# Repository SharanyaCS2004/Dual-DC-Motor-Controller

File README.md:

# 🚗 Dual DC Motor Controller (L298N-based)

This project is a simple and efficient **dual DC motor driver module** based on the **L298N** IC. It's designed to drive two DC motors with full H-bridge control and includes protection diodes and input/output connectors. Ideal for robotics kits, embedded systems, and motor control learners.

---

## 📦 Features

- ✅ Based on L298N dual H-bridge motor driver IC  
- ✅ Supports 2 DC motors with direction control  
- ✅ Optional PWM speed control via ENA/ENB  
- ✅ Flyback diodes (1N4007) for protection  
- ✅ Terminal blocks for motors and power  
- ✅ Logic level input via header pins  
- ✅ 2-layer compact PCB layout

---

## 🧠 Skills Demonstrated

- High-current trace routing  
- Silkscreen clarity for connectors  
- Power and thermal management  
- Modular and testable design

---

## ⚙️ Schematic Overview

- Motor driver: **L298N**
- Input voltage: **12V** regulated to **5V** using **7805**
- Control pins: **IN1–IN4**, **ENA**, **ENB**
- Output pins: **OUT1–OUT4** to motors
- Protection: **1N4007 diodes** for back-EMF across motor terminals

---

## 🔌 Pin Configuration

| Pin        | Function         |
|------------|------------------|
| IN1–IN4    | Direction control|
| ENA / ENB  | Enable/PWM input |
| OUT1–OUT4  | Motor outputs    |
| VS         | Motor power (12V)|
| VSS        | Logic power (5V) |
| GND        | Ground           |

---

## 📁 File Structure
``` Dual DC Motor Controller/
├── Dual DC Motor Controller.kicad_sch # Schematic file
├── Dual DC Motor Controller.kicad_pcb # PCB layout file
├── Dual DC Motor Controller.kicad_pro # KiCad project file
├── Dual DC Motor Controller.kicad_prl # KiCad netlist-related
├── Dual DC Motor Controller.kicad_sch-bak # Schematic backup
├── fp-info-cache # KiCad footprint cache
├── gerber/ # Gerber manufacturing files
├── Images/
│ ├── DUAL DC MOTOR 3D VIEW.png # 3D rendered board view
│ ├── DUAL DC MOTOR CONTROLLER_CKT.png # Schematic image
│ └── DUAL DC MOTOR CONTROLLER_PCB ROUTING.png # PCB routing image
└── README.md
```

## ⚙️ Features

- ✅ Dual motor control using **L298N**
- ✅ **Direction + Speed control** via logic pins and PWM (ENA/ENB)
- ✅ **Flyback protection diodes** (1N4007) for back EMF
- ✅ **12V motor supply**, regulated **5V logic supply** via L7805
- ✅ Screw terminal blocks for easy motor/power wiring
- ✅ Labelled headers for microcontroller interfacing

---

## 🔌 Pin Mapping

| Pin Name | Description              |
|----------|--------------------------|
| IN1–IN4  | Motor direction control  |
| ENA, ENB | Motor speed (PWM optional) |
| OUT1–OUT4 | Motor output to M1/M2   |
| VS       | Motor power input (12V)  |
| VSS      | Logic voltage (5V from 7805) |
| GND      | Common ground            |

---

## 🛠 Skills Demonstrated

- High-current trace routing
- Proper diode protection for inductive loads
- Clean schematic and silkscreen design
- 2-layer board optimization for thermal and space

---

 ## 🖼 Preview

🔧 Circuit Schematic  

### 🧩 PCB Routing  

### 🧱 3D View  

---

## 📄 License

This project is licensed under the [MIT License](LICENSE).

---

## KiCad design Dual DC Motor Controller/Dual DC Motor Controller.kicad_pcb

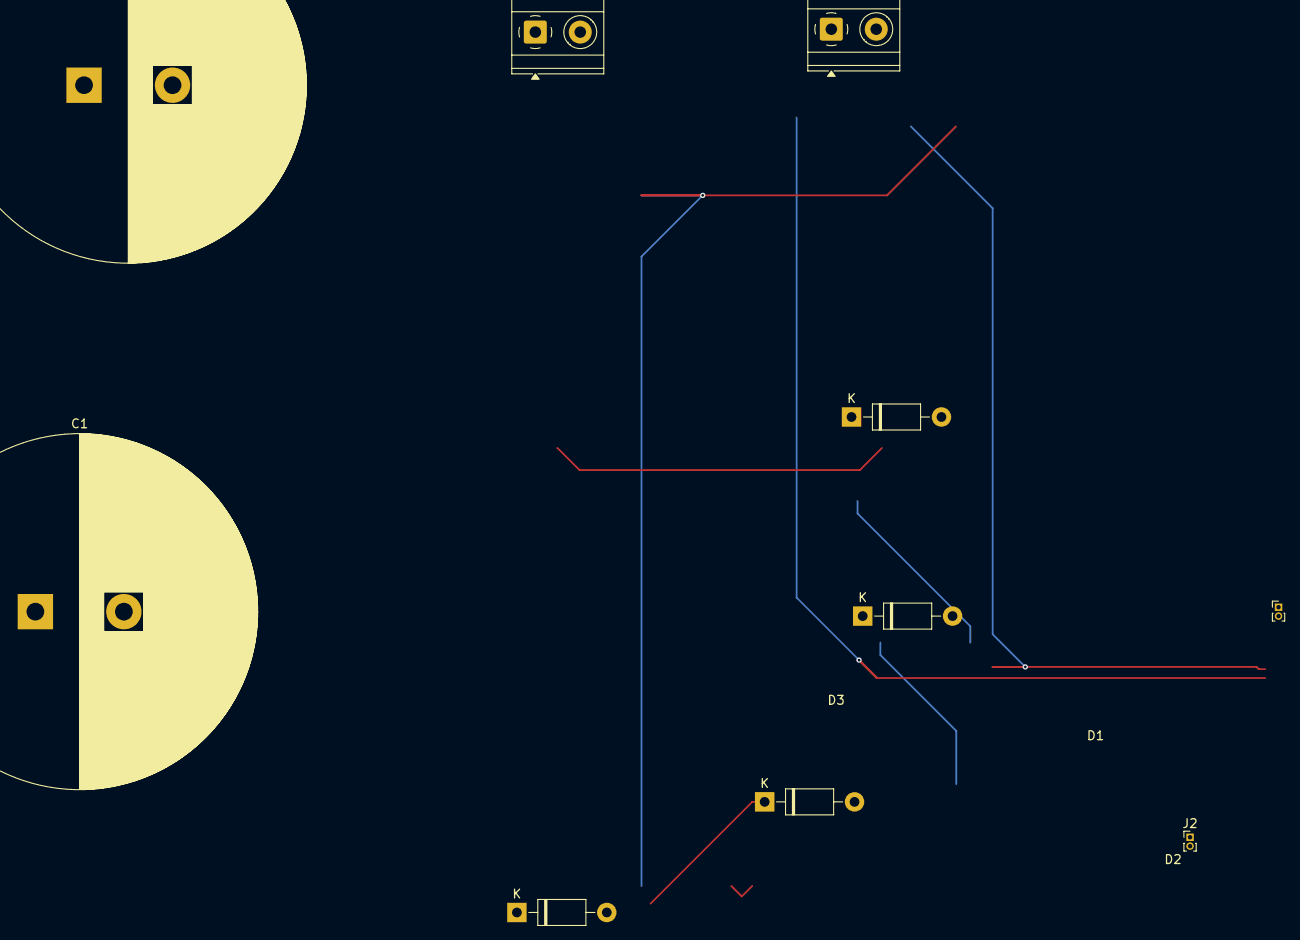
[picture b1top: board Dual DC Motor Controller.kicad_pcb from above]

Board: 2 copper layers, 10 parts (0 on the bottom side), 7 nets.

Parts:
C1: 100uF; CP_Radial_D40.0mm_P10.00mm_SnapIn
D1, D2, D3, D4: 1N4007; D_DO-41_SOD81_P10.16mm_Horizontal
J1: 12v; CP_Radial_D40.0mm_P10.00mm_SnapIn
J2: Conn_01x04; PinHeader_1x02_P1.00mm_Vertical
J4: Conn_01x02; PinHeader_1x02_P1.00mm_Vertical
M3, M4: Motor_DC; TerminalBlock_Phoenix_MKDS-1,5-2-5.08_1x02_P5.08mm_Horizont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

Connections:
GND: C1.2, D4.1 (K), J1.2, M4.2 (-)
unnamed: C1.1, D1.2 (A)
unnamed: D1.1 (K), D2.2 (A)
unnamed: D2.1 (K), D3.2 (A)
unnamed: D3.1 (K), D4.2 (A)
unnamed: J4.1, M4.1 (+)
unnamed: J4.2, M3.2 (-)

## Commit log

2025-07-02 Create 1
2025-07-02 Rename DUAL DC MOTOR 3D VIEW.png to 3DVIEW.png
2025-07-02 Rename DUAL DC MOTOR CONTROLLER_CKT.png to DUAL_DC_MOTOR_CONTROLLER_CKT.png
2025-07-02 Rename DUAL DC MOTOR CONTROLLER_PCB ROUTING.png to DUAL_DC_MOTOR_CONTROLLER_PCB_ROUTING.png
